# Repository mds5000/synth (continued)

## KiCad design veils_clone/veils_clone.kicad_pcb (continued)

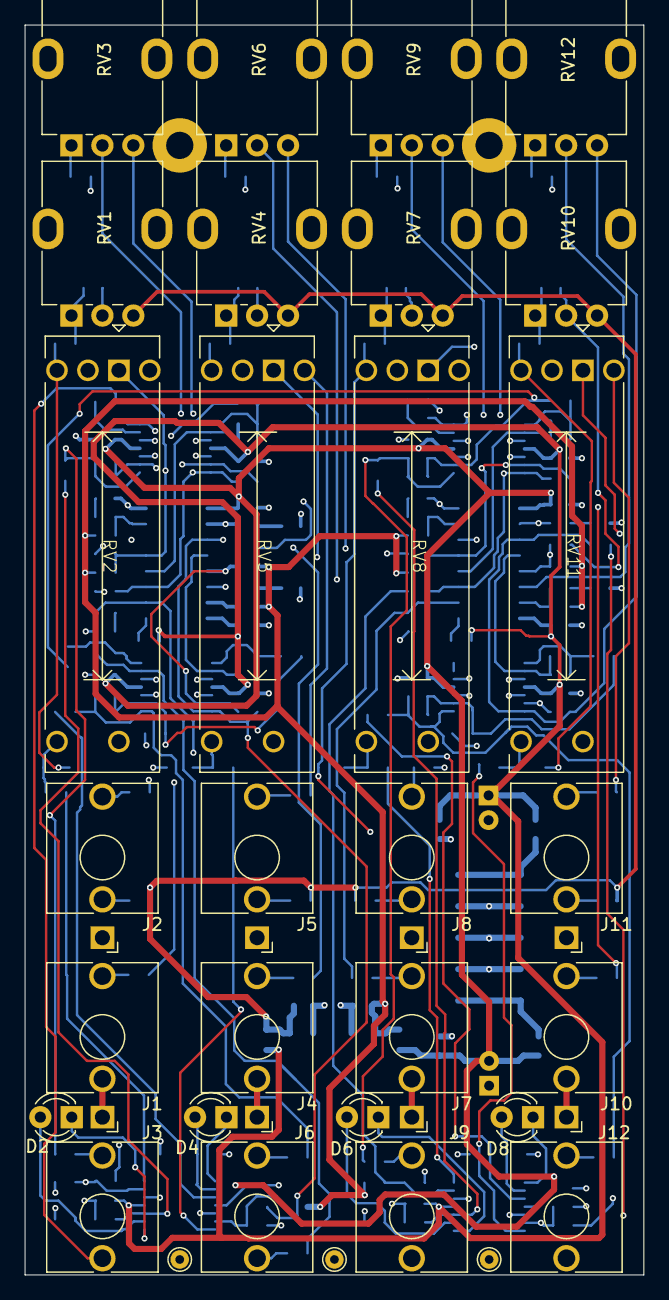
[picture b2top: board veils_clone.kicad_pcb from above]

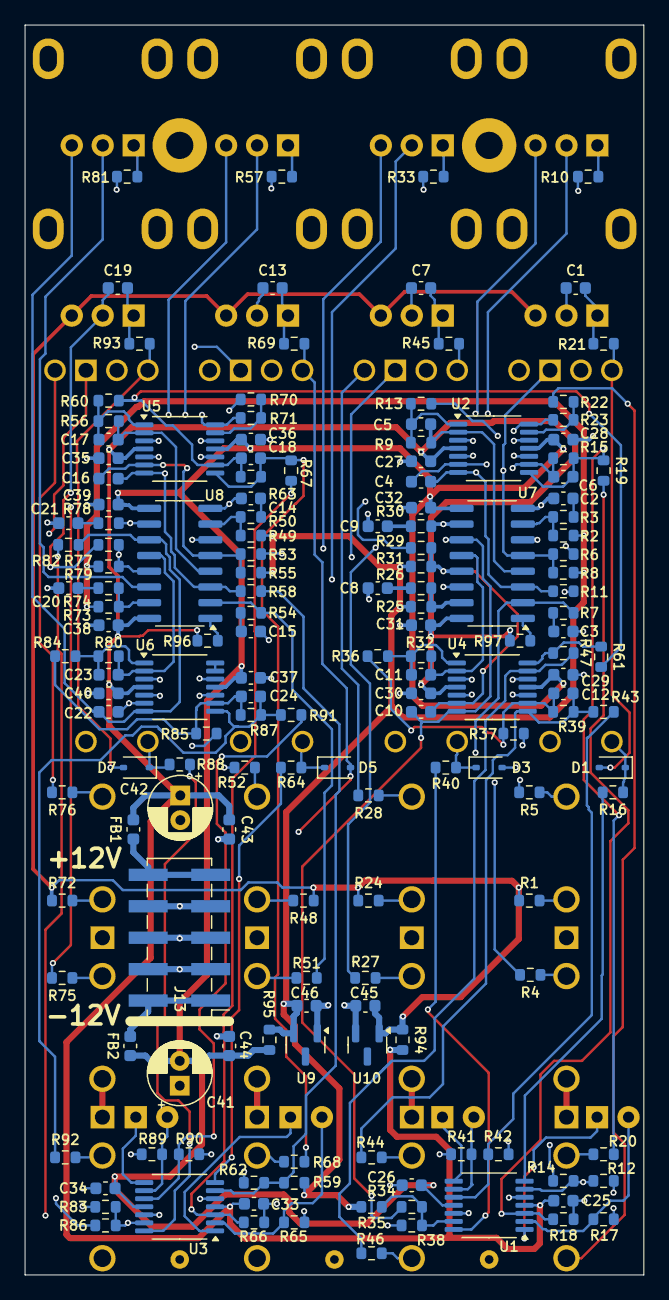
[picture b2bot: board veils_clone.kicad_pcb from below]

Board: 4 copper layers, 50.0 x 101.0 mm, 188 parts (160 on the bottom side), 119 nets.

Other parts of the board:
R71: 5.1K; R_0603_1608Metric

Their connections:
/CH3/OUT: R71.2; also elsewhere on the board
unnamed 96: R71.1; also elsewhere on the board

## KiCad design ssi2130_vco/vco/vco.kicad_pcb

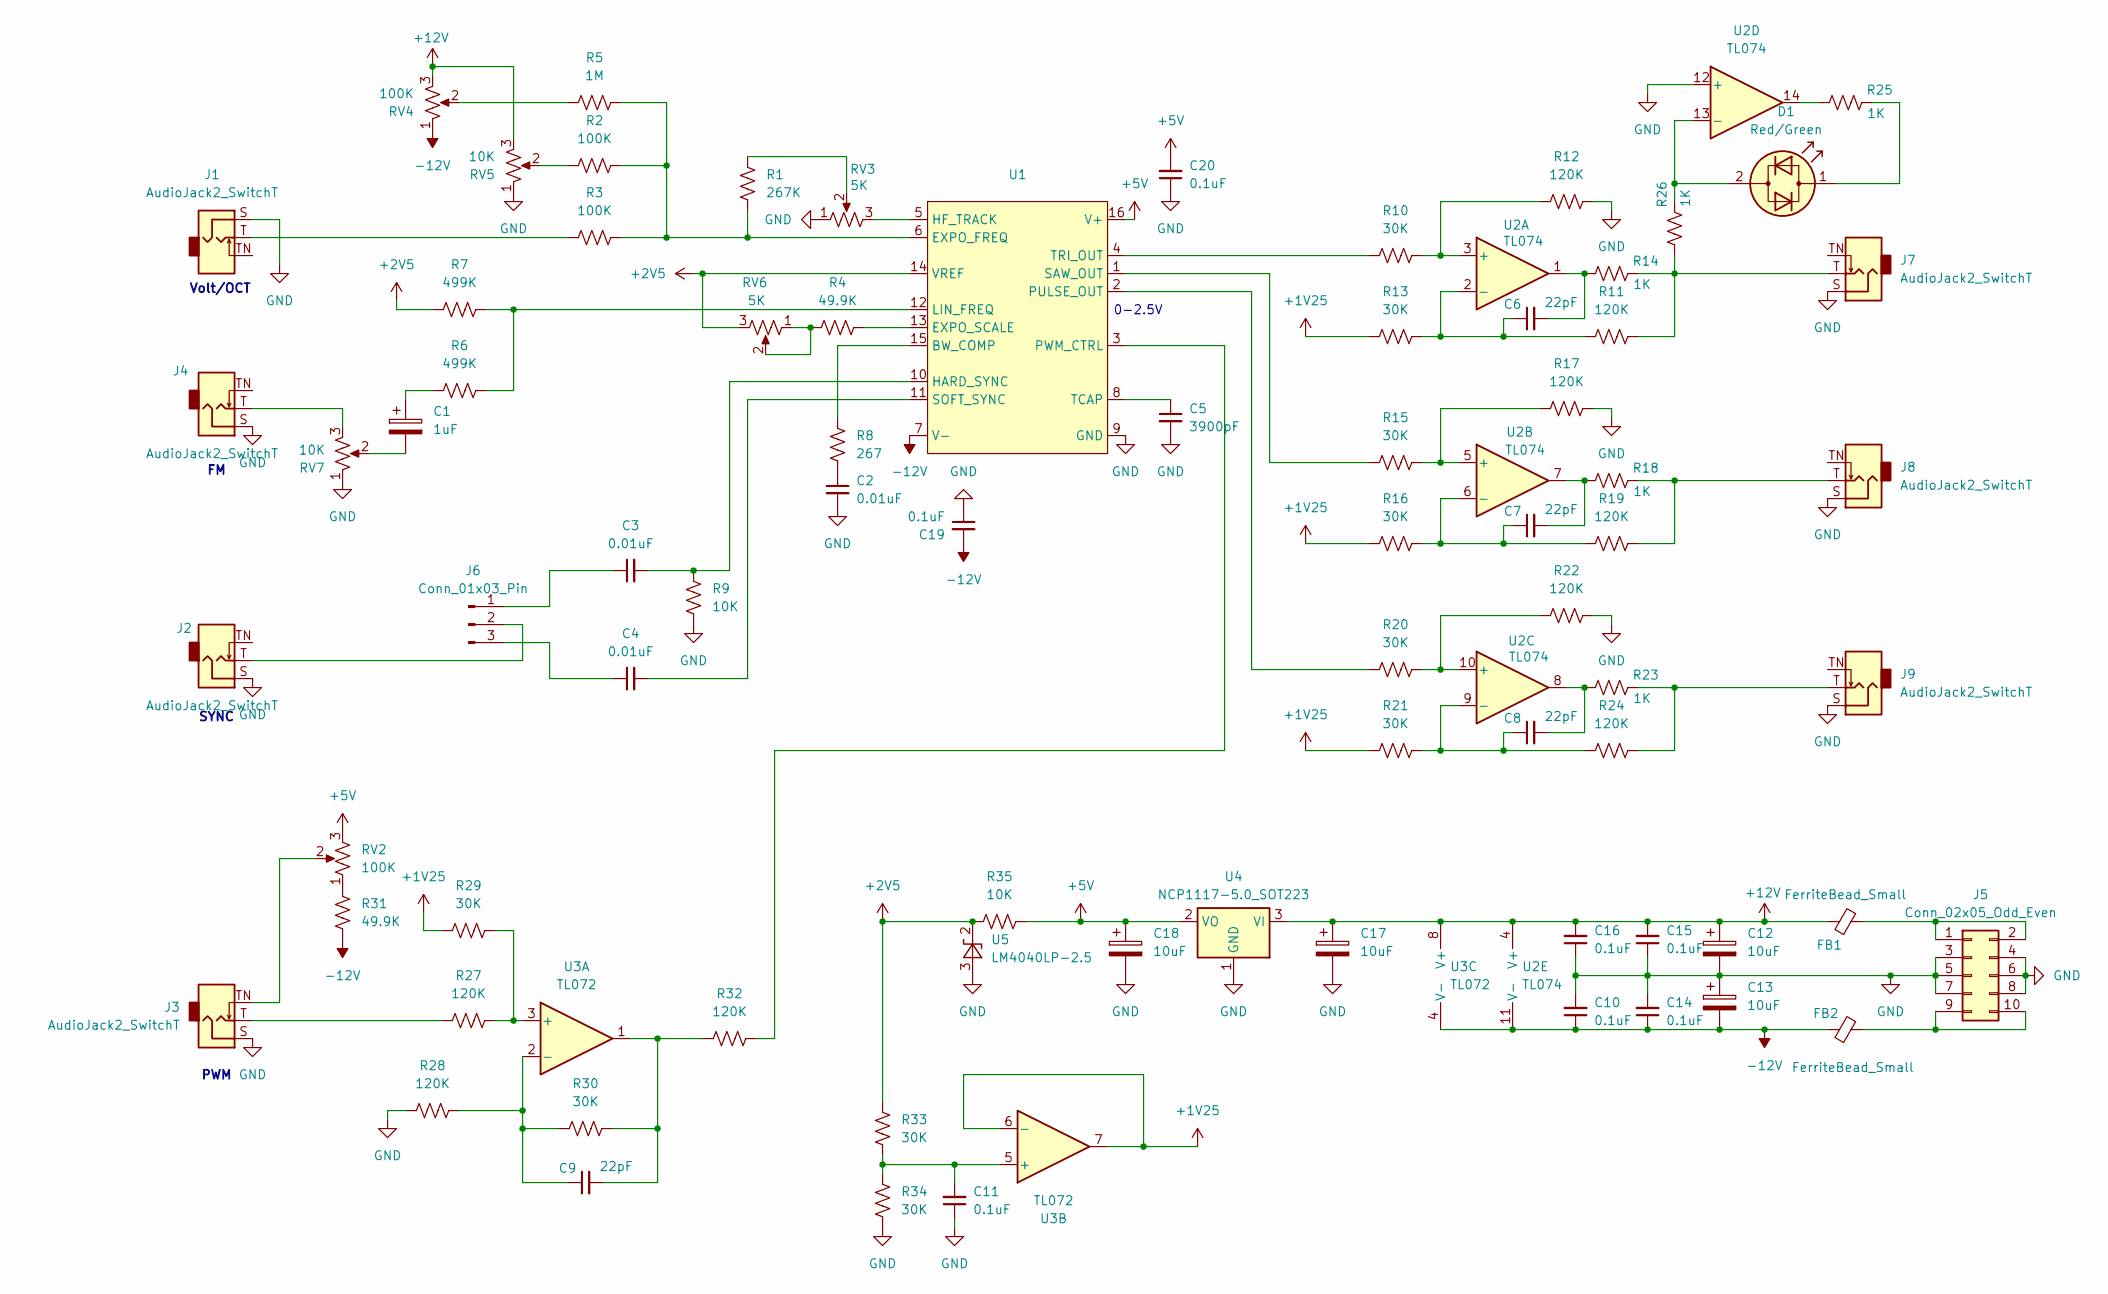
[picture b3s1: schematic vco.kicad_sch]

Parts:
C1: 1uF; CP_Radial_D5.0mm_P2.00mm
C2, C3, C4: 0.01uF; C_0603_1608Metric_Pad1.08x0.95mm_HandSolder
C5: 3900pF; C_0603_1608Metric_Pad1.08x0.95mm_HandSolder
C6, C7, C8, C9: 22pF; C_0603_1608Metric_Pad1.08x0.95mm_HandSolder
C10, C11, C14, C15, C16, C19, C20: 0.1uF; C_0603_1608Metric_Pad1.08x0.95mm_HandSolder
C12, C13, C17, C18: 10uF; CP_Radial_D5.0mm_P2.00mm
D1: Red/Green; LED_D3.0mm
FB1, FB2: FerriteBead_Small; R_0603_1608Metric_Pad0.98x0.95mm_HandSolder
J1, J2, J3, J4, J7, J8, J9: AudioJack2_SwitchT; Jack_3.5mm_QingPu_WQP-PJ398SM_Vertical_CircularHoles
J5: Conn_02x05_Odd_Even; PinHeader_2x05_P2.54mm_Vertical
J6: Conn_01x03_Pin; PinHeader_1x03_P2.54mm_Vertical
R1: 267K; R_0603_1608Metric_Pad0.98x0.95mm_HandSolder
R2, R3: 100K; R_0603_1608Metric_Pad0.98x0.95mm_HandSolder
R4, R31: 49.9K; R_0603_1608Metric_Pad0.98x0.95mm_HandSolder
R5: 1M; R_0603_1608Metric_Pad0.98x0.95mm_HandSolder
R6, R7: 499K; R_0603_1608Metric_Pad0.98x0.95mm_HandSolder
R8: 267; R_0603_1608Metric_Pad0.98x0.95mm_HandSolder
R9, R35: 10K; R_0603_1608Metric_Pad0.98x0.95mm_HandSolder
R10, R13, R15, R16, R20, R21, R29, R30, R33, R34: 30K; R_0603_1608Metric_Pad0.98x0.95mm_HandSolder
R11, R12, R17, R19, R22, R24, R27, R28, R32: 120K; R_0603_1608Metric_Pad0.98x0.95mm_HandSolder
R14, R18, R23, R25, R26: 1K; R_0603_1608Metric_Pad0.98x0.95mm_HandSolder
RV2, RV4: 100K; Potentiometer_Alpha_RD901F-40-00D_Single_Vertical
RV3, RV6: 5K; Potentiometer_Bourns_3296W_Vertical
RV5, RV7: 10K; Potentiometer_Alpha_RD901F-40-00D_Single_Vertical
U1: SOIC-16_3.9x9.9mm_P1.27mm
U2: TL074; SOIC-14_3.9x8.7mm_P1.27mm
U3: TL072; SOIC-8_3.9x4.9mm_P1.27mm
U4: NCP1117-5.0_SOT223; SOT-223-3_TabPin2
U5: LM4040LP-2.5; TO-92_Inline

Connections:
+1V25: R13.2, R16.2, R21.2, R29.2, U3.6 (-), U3.7
+2V5: R7.1, R33.1, R35.2, RV6.3, U1.14 (VREF), U5.2 (K)
+5V: C18.1, C20.2, R35.1, RV2.3, U1.16 (V+), U4.2 (VO)
+12V: C12.1, C15.2, C16.2, C17.1, FB1.1, RV4.3, RV5.3, U2.4 (V+), U3.8 (V+), U4.3 (VI)
-12V: C10.1, C13.2, C14.1, C19.2, FB2.1, R31.1, RV4.1, U1.7 (V-), U2.11 (V-), U3.4 (V-)
GND: C2.2, C5.2, C10.2, C11.1, C12.2, C13.1, C14.2, C15.1, C16.1, C17.2, C18.2, C19.1, C20.1, J1.S, J2.S, J3.S, J4.S, J5.3, J5.4, J5.5, J5.6, J5.7, J5.8, J7.S, J8.S, J9.S, R9.1, R12.1, R17.1, R22.1, R28.2, R34.2, RV3.1, RV5.1, RV7.1, U1.9 (GND), U2.12 (+), U4.1 (GND), U5.3 (A)
unnamed: C1.1, R6.1
unnamed: C1.2, RV7.2
unnamed: C2.1, R8.1
unnamed: C6.2, R14.2, U2.1
unnamed: C7.2, R18.2, U2.7
unnamed: C8.2, R23.2, U2.8
unnamed: C9.2, R30.1, R32.2, U3.1
unnamed: D1.2 (AK), R26.1, U2.13 (-)
unnamed: D1.1 (KA), R25.1
unnamed: J1.T, R3.1
unnamed: J3.T, R27.2
unnamed: J3.TN, RV2.2
unnamed: J4.T, RV7.3
unnamed: FB1.2, J5.1, J5.2
unnamed: FB2.2, J5.9, J5.10
unnamed: C3.1, J6.1
unnamed: J2.T, J6.2
unnamed: C4.1, J6.3
unnamed: J7.T, R11.1, R14.1, R26.2
unnamed: J8.T, R18.1, R19.1
unnamed: J9.T, R23.1, R24.1
unnamed: R1.2, RV3.2
unnamed: R2.1, RV5.2
unnamed: R4.1, RV6.1, RV6.2
unnamed: R5.1, RV4.2
unnamed: R25.2, U2.14
unnamed: R31.2, RV2.1
unnamed: R8.2, U1.15 (BW_COMP)
unnamed: R1.1, R2.2, R3.2, R5.2, U1.6 (EXPO_FREQ)
unnamed: R4.2, U1.13 (EXPO_SCALE)
unnamed: C3.2, R9.2, U1.10 (HARD_SYNC)
unnamed: RV3.3, U1.5 (HF_TRACK)
unnamed: R6.2, R7.2, U1.12 (LIN_FREQ)
unnamed: R20.2, U1.2 (PULSE_OUT)
unnamed: R32.1, U1.3 (PWM_CTRL)
unnamed: R15.2, U1.1 (SAW_OUT)
unnamed: C4.2, U1.11 (SOFT_SYNC)
unnamed: C5.1, U1.8 (TCAP)
unnamed: R10.2, U1.4 (TRI_OUT)
unnamed: R10.1, R12.2, U2.3 (+)
unnamed: C6.1, R11.2, R13.1, U2.2 (-)
unnamed: R15.1, R17.2, U2.5 (+)
unnamed: C7.1, R16.1, R19.2, U2.6 (-)
unnamed: R20.1, R22.2, U2.10 (+)
unnamed: C8.1, R21.1, R24.2, U2.9 (-)
unnamed: R27.1, R29.1, U3.3 (+)
unnamed: C9.1, R28.1, R30.2, U3.2 (-)
unnamed: C11.2, R33.2, R34.1, U3.5 (+)

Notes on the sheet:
0-2.5V
SYNC
Volt/OCT
PWM

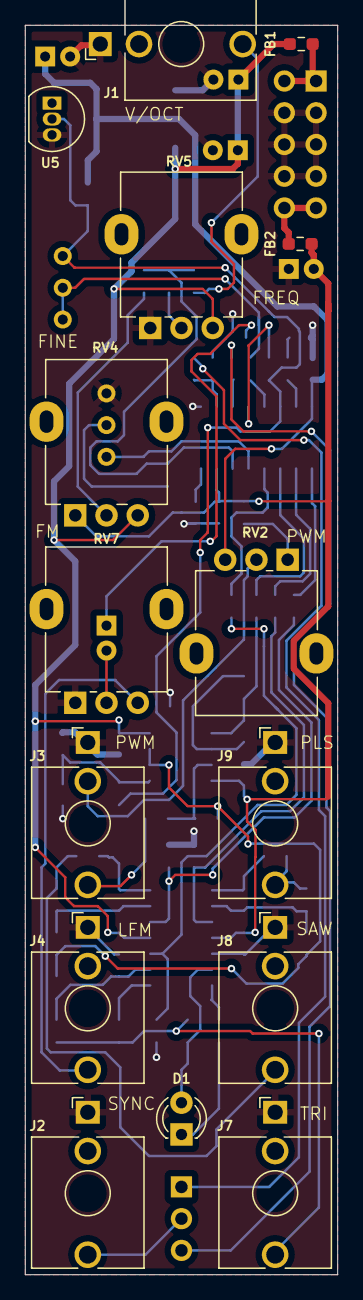
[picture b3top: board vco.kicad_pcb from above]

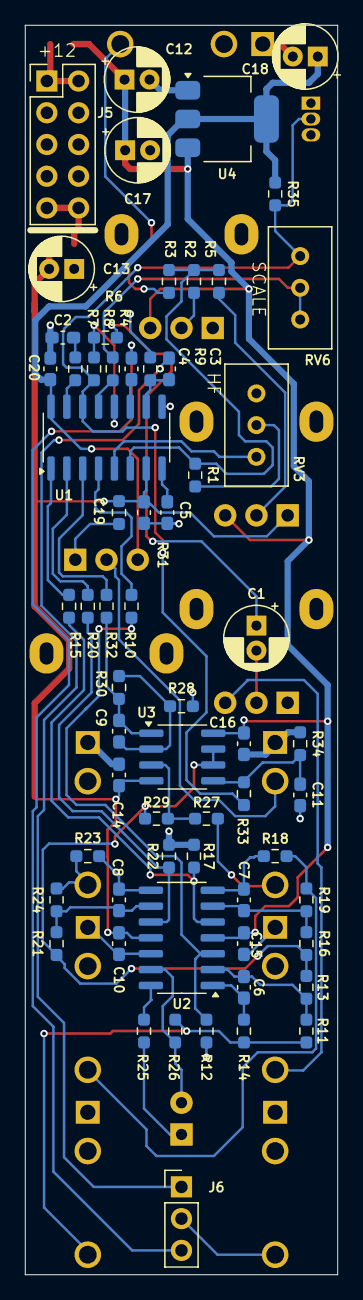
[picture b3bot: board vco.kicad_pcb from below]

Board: 2 copper layers, 25.0 x 100.0 mm, 78 parts (63 on the bottom side), 54 nets.

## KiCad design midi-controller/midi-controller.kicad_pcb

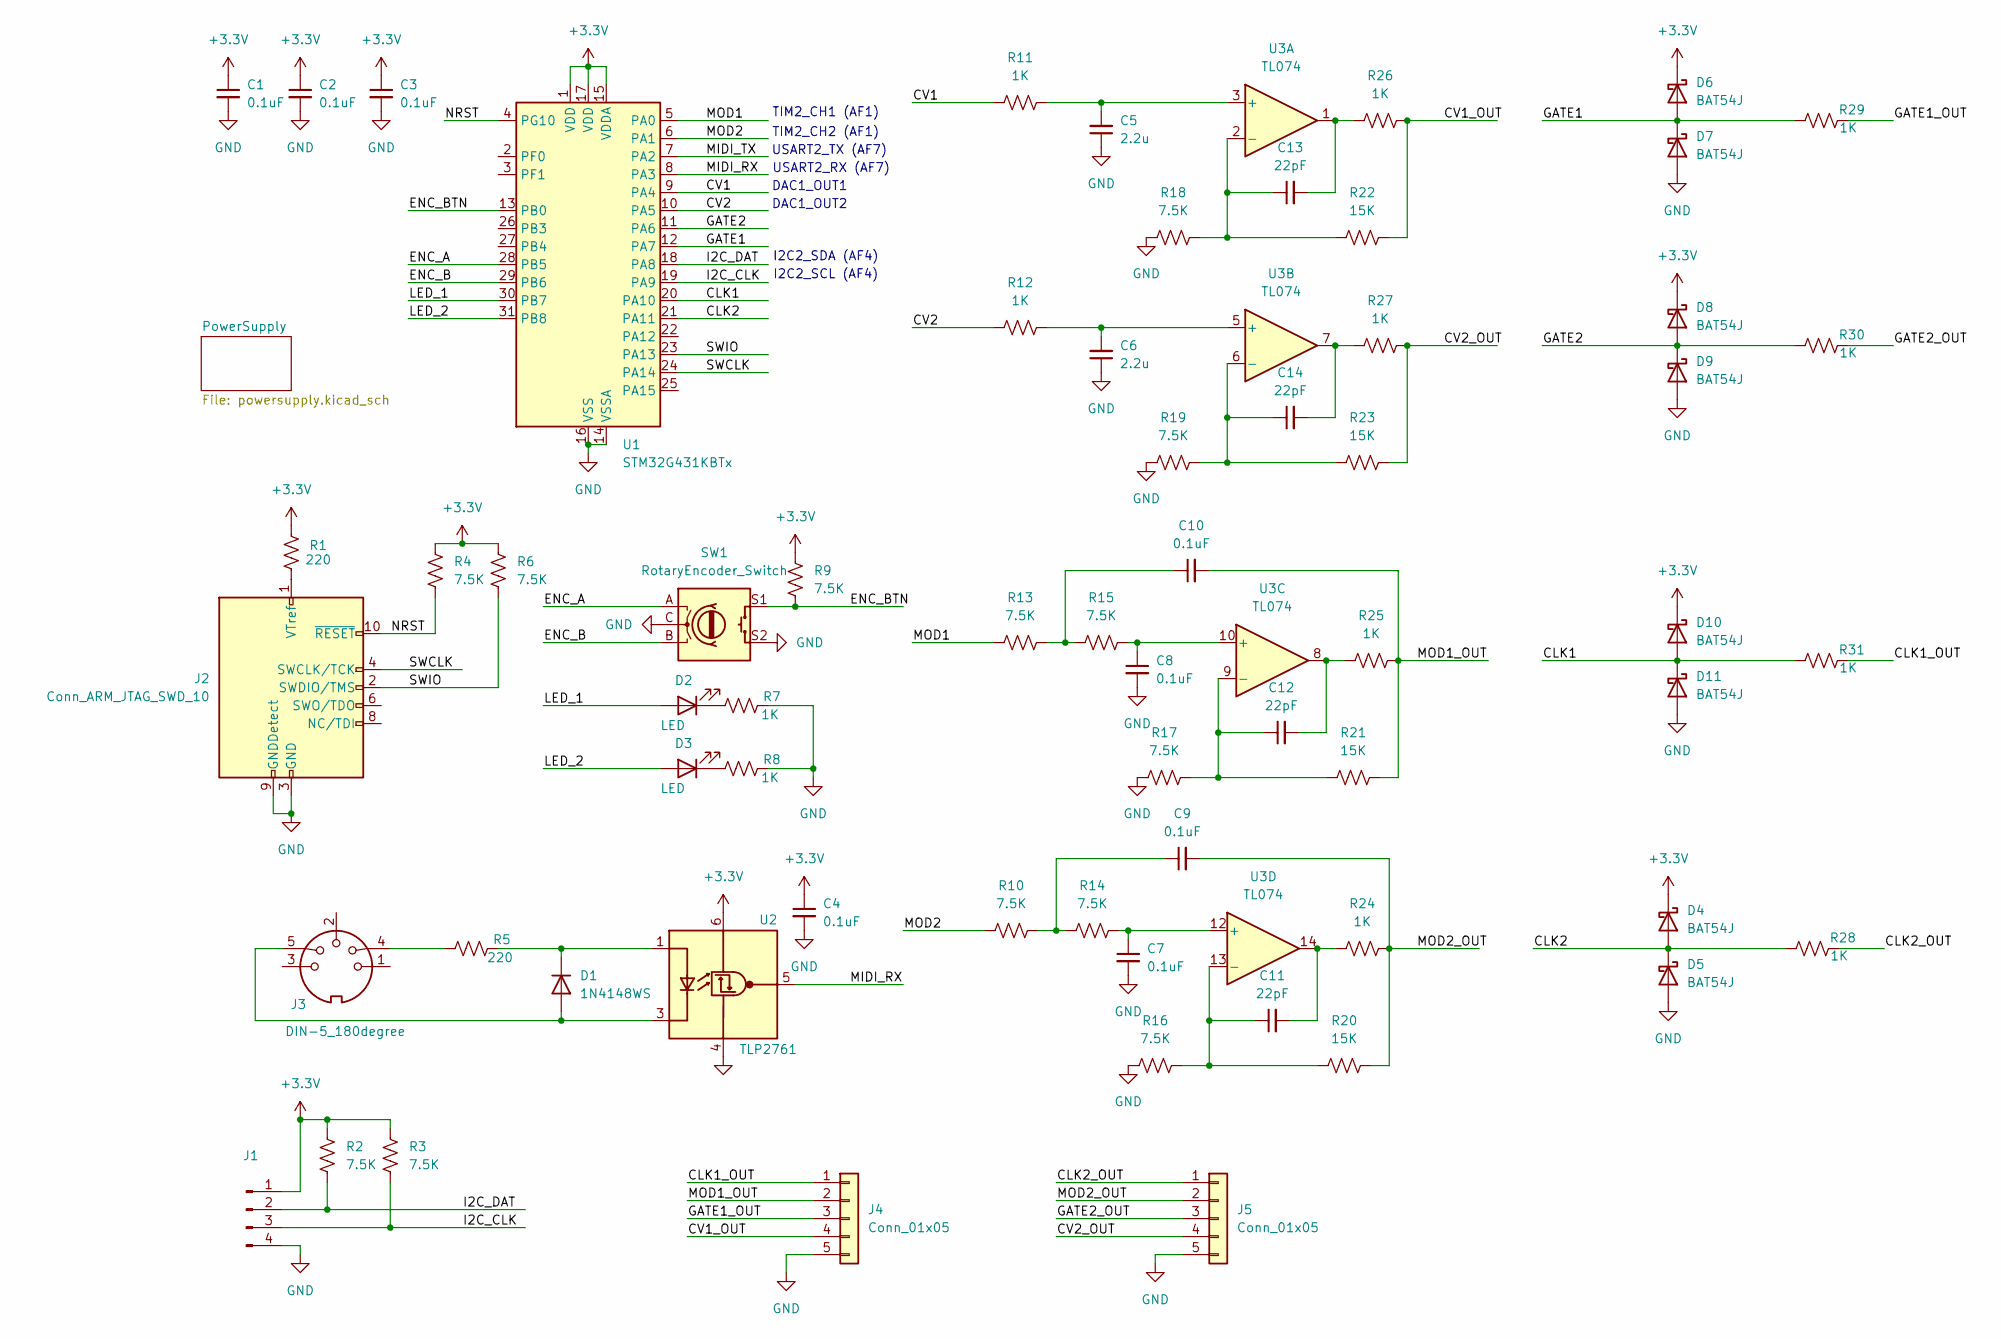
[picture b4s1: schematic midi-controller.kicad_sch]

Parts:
C1, C2, C3, C4, C7, C8, C9, C10: 0.1uF; C_0603_1608Metric
C5, C6: 2.2u; C_0805_2012Metric
C11, C12, C13, C14: 22pF; C_0603_1608Metric
D1: 1N4148WS; D_SOD-323
D2, D3: LED; LED_0603_1608Metric
D4, D5, D6, D7, D8, D9, D10, D11: BAT54J; D_SOD-323F
J1: Conn_01x04_Pin; PinHeader_1x04_P2.54mm_Vertical
J2: Conn_ARM_JTAG_SWD_10; PinHeader_2x05_P1.27mm_Vertical
J3: DIN-5_180degree; MIDI_DIN5
J4, J5: Conn_01x05; JST_XH_B5B-XH-A_1x05_P2.50mm_Vertical
R1, R5: 220; R_0603_1608Metric
R2, R3, R4, R6, R9, R10, R13, R14, R15, R16, R17, R18, R19: 7.5K; R_0603_1608Metric
R7, R8, R11, R12, R24, R25, R26, R27, R28, R29, R30, R31: 1K; R_0603_1608Metric
R20, R21, R22, R23: 15K; R_0603_1608Metric
SW1: RotaryEncoder_Switch; RotaryEncoder_Alps_EC11E-Switch_Vertical_H20mm
U1: STM32G431KBTx; LQFP-32_7x7mm_P0.8mm
U2: TLP2761; SO-6L_10x3.84mm_P1.27mm
U3: TL074; SOIC-14_3.9x8.7mm_P1.27mm

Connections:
+3.3V: C1.1, C2.1, C3.1, C4.1, D4.1 (K), D6.1 (K), D8.1 (K), D10.1 (K), J1.1, R1.1, R2.1, R3.1, R4.1, R6.1, R9.1, U1.1 (VDD), U1.15 (VDDA), U1.17 (VDD), U2.6 (VDD); also elsewhere on the board
/CLK1: D10.2 (A), D11.1 (K), R31.2, U1.20 (PA10)
/CLK1_OUT: J4.1, R31.1
/CLK2: D4.2 (A), D5.1 (K), R28.2, U1.21 (PA11)
/CLK2_OUT: J5.1, R28.1
/CV1: R11.2, U1.9 (PA4)
/CV1_OUT: J4.4, R22.1, R26.1
/CV2: R12.2, U1.10 (PA5)
/CV2_OUT: J5.4, R23.1, R27.1
/ENC_A: SW1.A, U1.28 (PB5)
/ENC_B: SW1.B, U1.29 (PB6)
/ENC_BTN: R9.2, SW1.S1, U1.13 (PB0)
/GATE1: D6.2 (A), D7.1 (K), R29.2, U1.12 (PA7)
/GATE1_OUT: J4.3, R29.1
/GATE2: D8.2 (A), D9.1 (K), R30.2, U1.11 (PA6)
/GATE2_OUT: J5.3, R30.1
/I2C_CLK: J1.3, R3.2, U1.19 (PA9)
/I2C_DAT: J1.2, R2.2, U1.18 (PA8)
/LED_1: D2.2 (A), U1.30 (PB7)
/LED_2: D3.2 (A), U1.31 (PB8)
/MIDI_RX: U1.8 (PA3), U2.5 (VO)
/MIDI_TX: U1.7 (PA2)
/MOD1: R13.2, U1.5 (PA0)
/MOD1_OUT: C10.2, J4.2, R21.1, R25.1
/MOD2: R10.2, U1.6 (PA1)
/MOD2_OUT: C9.2, J5.2, R20.1, R24.1
/NRST: J2.10 (~RESET), R4.2, U1.4 (PG10)
/SWCLK: J2.4 (SWCLK/TCK), U1.24 (PA14)
/SWIO: J2.2 (SWDIO/TMS), R6.2, U1.23 (PA13)
GND: C1.2, C2.2, C3.2, C4.2, C5.1, C6.1, C7.2, C8.2, D5.2 (A), D7.2 (A), D9.2 (A), D11.2 (A), J1.4, J2.3 (GND), J2.5 (GND), J2.9 (GNDDetect), J4.5, J5.5, R7.1, R8.1, R16.2, R17.2, R18.2, R19.2, SW1.C, SW1.S2, U1.14 (VSSA), U1.16 (VSS), U1.32 (VSS), U2.4 (GND); also elsewhere on the board
unnamed: C9.1, R10.1, R14.2
unnamed: C10.1, R13.1, R15.2
unnamed: C11.2, R24.2, U3.14
unnamed: C12.2, R25.2, U3.8
unnamed: C13.2, R26.2, U3.1
unnamed: C14.2, R27.2, U3.7
unnamed: D1.2 (A), J3.5, U2.3 (K)
unnamed: D1.1 (K), R5.1, U2.1 (A)
unnamed: D2.1 (K), R7.2
unnamed: D3.1 (K), R8.2
unnamed: J2.1 (VTref), R1.2
unnamed: J3.4, R5.2
unnamed: C5.2, R11.1, U3.3 (+)
unnamed: C13.1, R18.1, R22.2, U3.2 (-)
unnamed: C6.2, R12.1, U3.5 (+)
unnamed: C14.1, R19.1, R23.2, U3.6 (-)
unnamed: C8.1, R15.1, U3.10 (+)
unnamed: C12.1, R17.1, R21.2, U3.9 (-)
unnamed: C7.1, R14.1, U3.12 (+)
unnamed: C11.1, R16.1, R20.2, U3.13 (-)

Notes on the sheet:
DAC1_OUT1
TIM2_CH1 (AF1)
TIM2_CH2 (AF1)
USART2_TX (AF7)
USART2_RX (AF7)
DAC1_OUT2
I2C2_SDA (AF4)
I2C2_SCL (AF4)

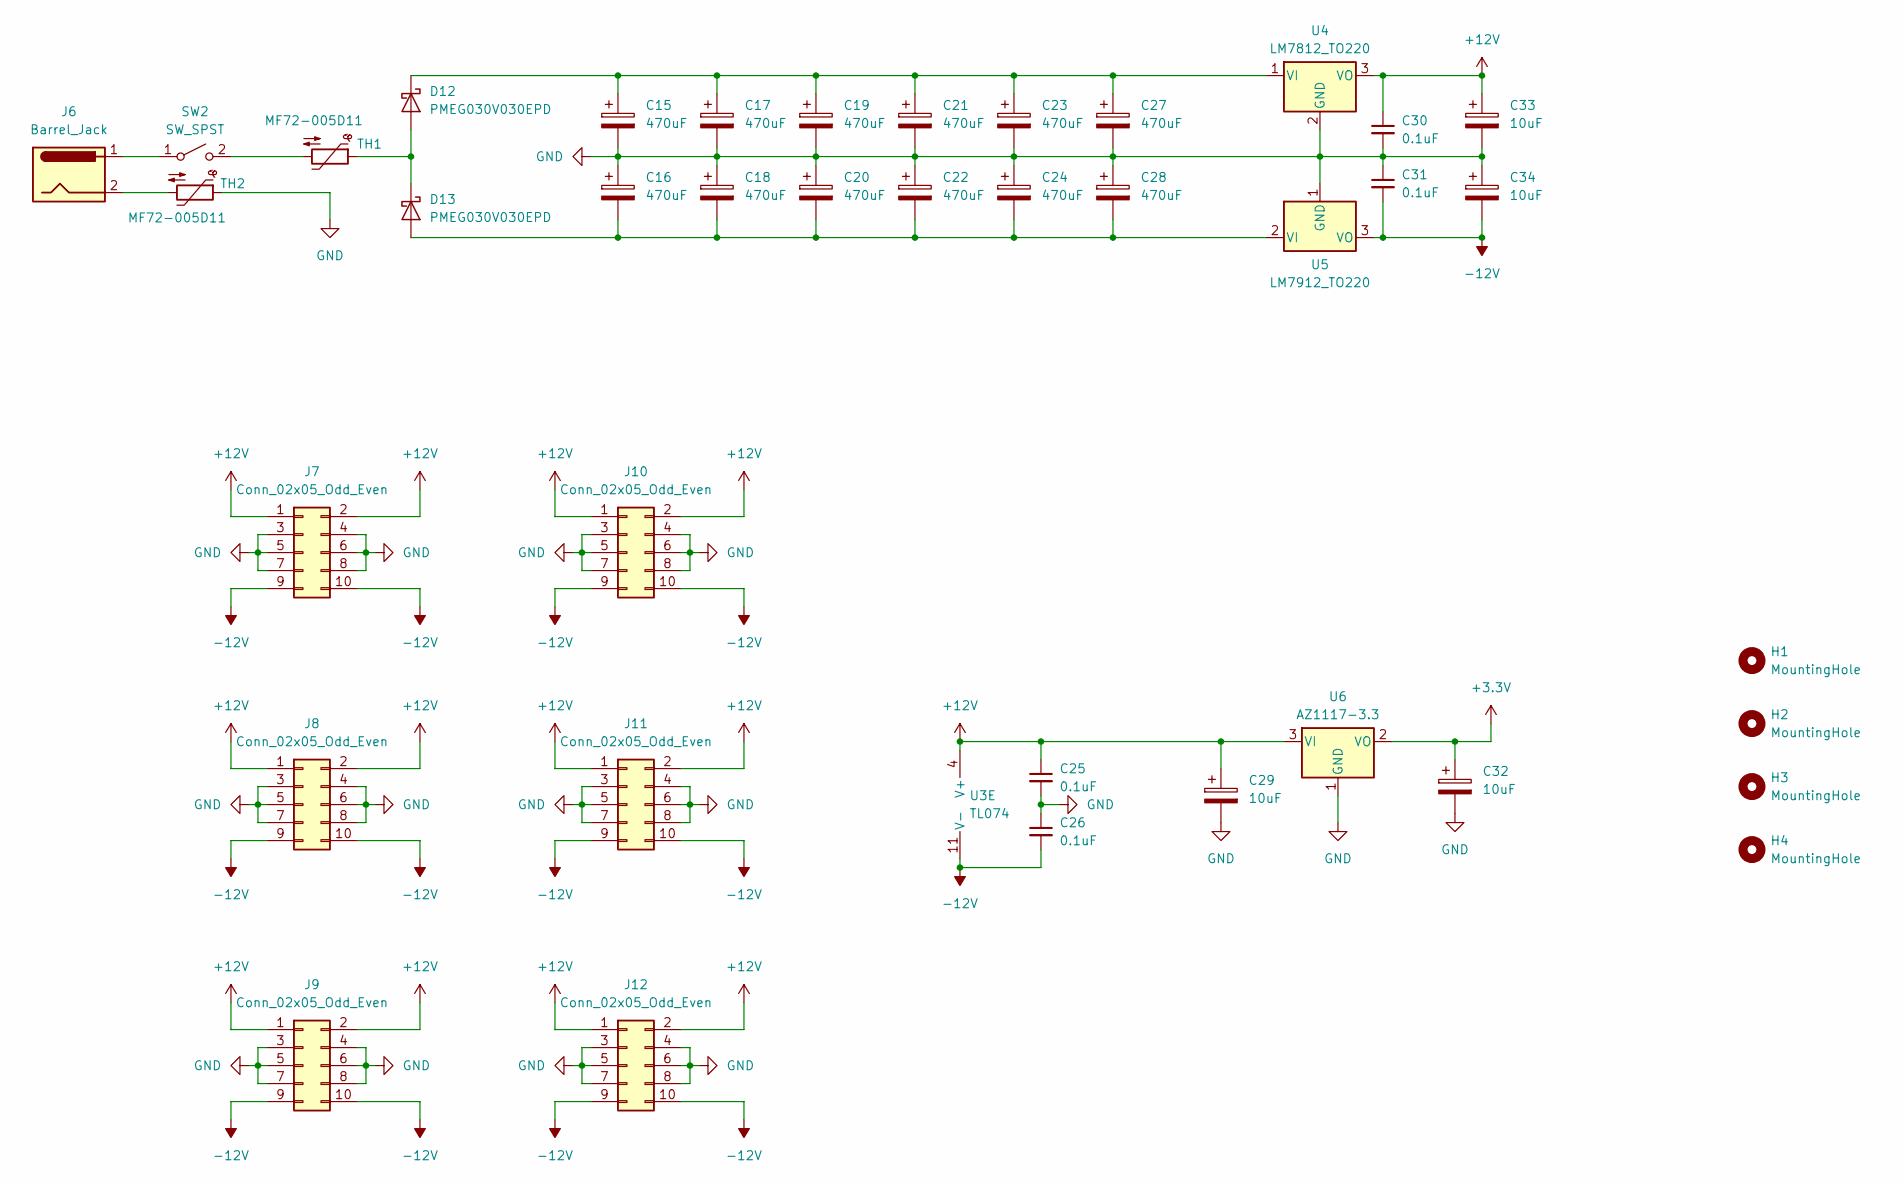
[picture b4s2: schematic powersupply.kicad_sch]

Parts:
C15, C16, C17, C18, C19, C20, C21, C22, C23, C24, C27, C28: 470uF; CP_Radial_D10.0mm_P5.00mm
C25, C26, C30, C31: 0.1uF; C_0603_1608Metric
C29, C32, C33, C34: 10uF; CP_Radial_D5.0mm_P2.00mm
D12, D13: PMEG030V030EPD; Nexperia_CFP15_SOT-1289
H1, H2, H3, H4: MountingHole; MountingHole_3.2mm_M3_Pad
J6: Barrel_Jack; BarrelJack_CUI_PJ-102AH_Horizontal
J7, J8, J9, J10, J11, J12: Conn_02x05_Odd_Even; PinHeader_2x05_P2.54mm_Vertical
SW2: SW_SPST; RA1H1C112R
TH1, TH2: MF72-005D11; RV_Disc_D12mm_W5.8mm_P7.5mm
U3: TL074; SOIC-14_3.9x8.7mm_P1.27mm
U4: LM7812_TO220; TO-220-3_Vertical
U5: LM7912_TO220; TO-220-3_Vertical
U6: AZ1117-3.3; TO-252-3_TabPin2

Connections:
+3.3V: C32.1, U6.2 (VO); also elsewhere on the board
+12V: C25.1, C29.1, C30.1, C33.1, J7.1, J7.2, J8.1, J8.2, J9.1, J9.2, J10.1, J10.2, J11.1, J11.2, J12.1, J12.2, U3.4 (V+), U4.3 (VO), U6.3 (VI)
-12V: C26.2, C31.2, C34.2, J7.9, J7.10, J8.9, J8.10, J9.9, J9.10, J10.9, J10.10, J11.9, J11.10, J12.9, J12.10, U3.11 (V-), U5.3 (VO)
GND: C15.2, C16.1, C17.2, C18.1, C19.2, C20.1, C21.2, C22.1, C23.2, C24.1, C25.2, C26.1, C27.2, C28.1, C29.2, C30.2, C31.1, C32.2, C33.2, C34.1, J7.3, J7.4, J7.5, J7.6, J7.7, J7.8, J8.3, J8.4, J8.5, J8.6, J8.7, J8.8, J9.3, J9.4, J9.5, J9.6, J9.7, J9.8, J10.3, J10.4, J10.5, J10.6, J10.7, J10.8, J11.3, J11.4, J11.5, J11.6, J11.7, J11.8, J12.3, J12.4, J12.5, J12.6, J12.7, J12.8, TH2.1, U4.2 (GND), U5.1 (GND), U6.1 (GND); also elsewhere on the board
unnamed: C15.1, C17.1, C19.1, C21.1, C23.1, C27.1, D12.3 (K), U4.1 (VI)
unnamed: D12.1 (A), D12.2 (A), D13.3 (K), TH1.1
unnamed: J6.2, TH2.2
unnamed: J6.1, SW2.1 (A)
unnamed: SW2.2 (B), TH1.2
unnamed: C16.2, C18.2, C20.2, C22.2, C24.2, C28.2, D13.1 (A), D13.2 (A), U5.2 (VI)

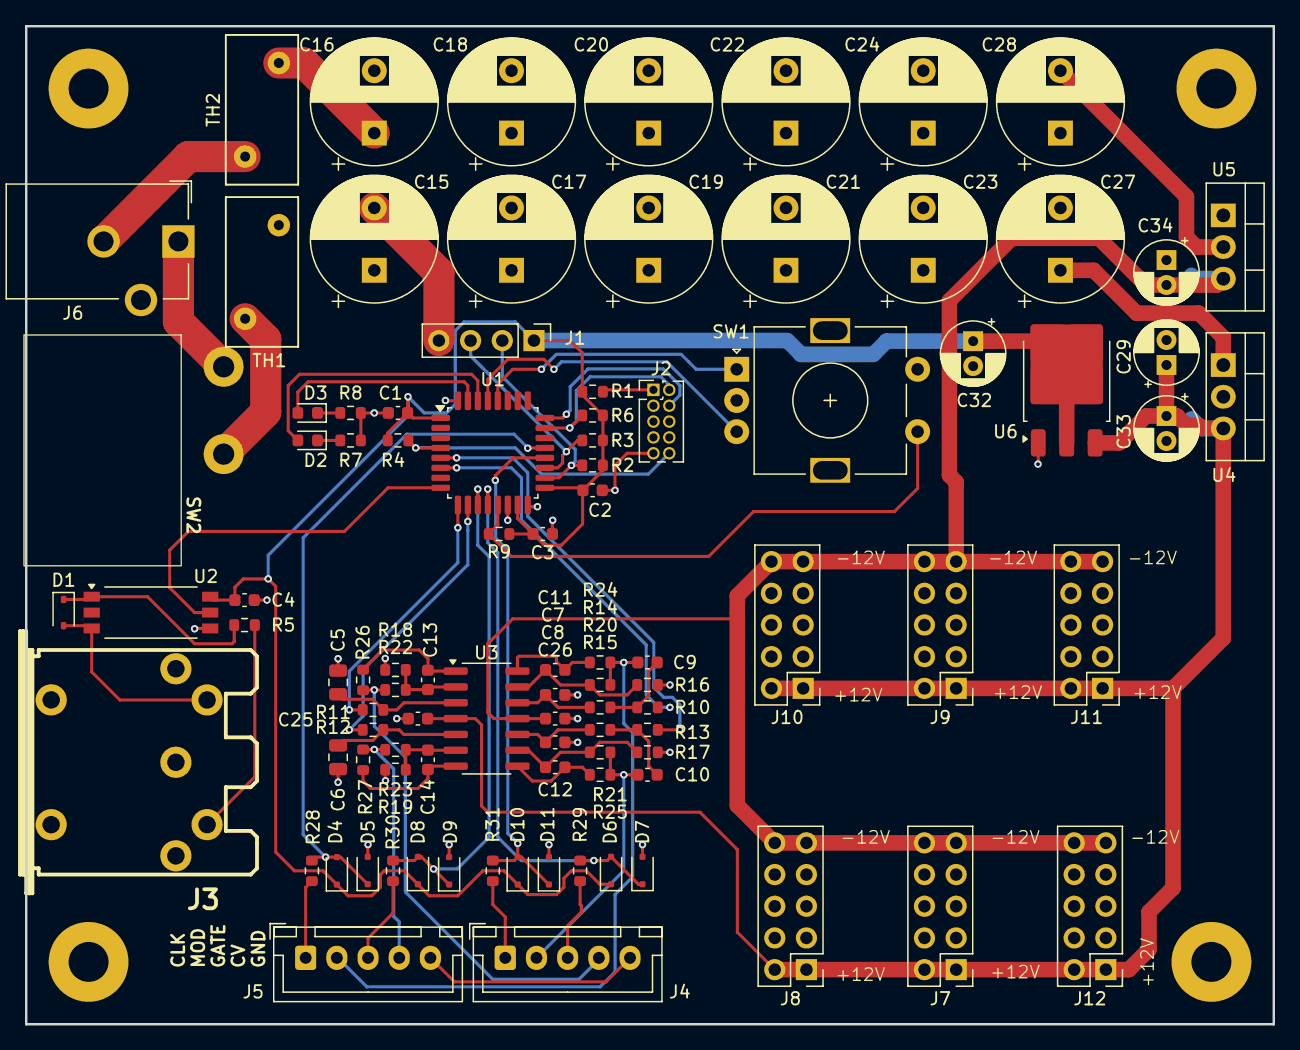
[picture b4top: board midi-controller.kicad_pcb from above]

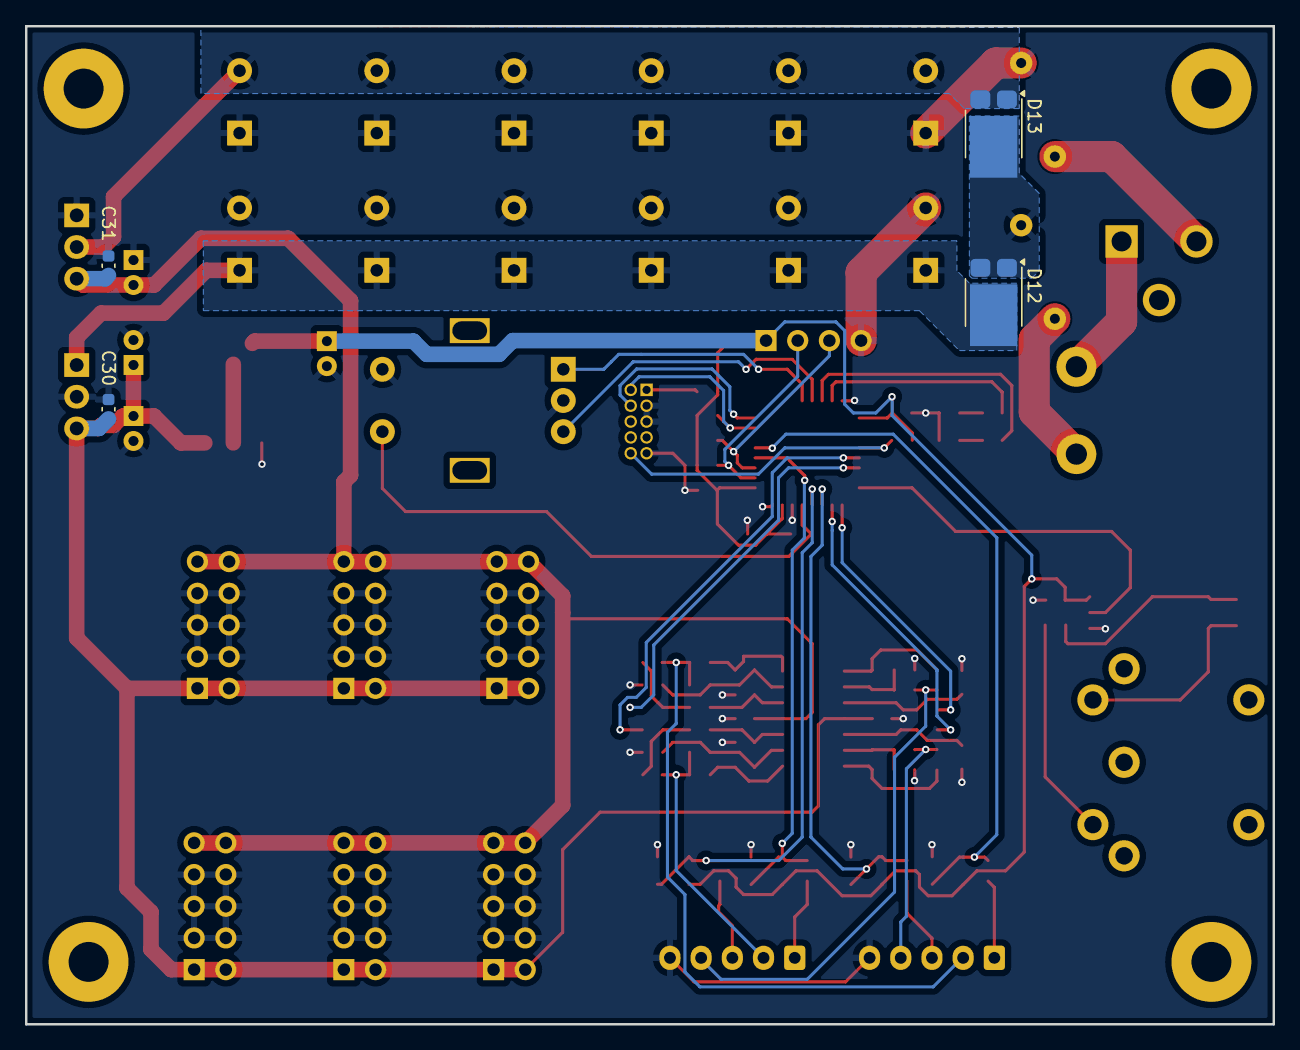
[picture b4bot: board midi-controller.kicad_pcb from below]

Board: 2 copper layers, 100.0 x 80.0 mm, 104 parts (4 on the bottom side), 57 nets.

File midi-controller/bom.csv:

"Reference","Value","Datasheet","Footprint","Qty","DNP"
"C1,C2,C3,C4,C7,C8,C9,C10,C25,C26,C30,C31","0.1uF","~","Capacitor_SMD:C_0603_1608Metric","12",""
"C5,C6","2.2u","~","Capacitor_SMD:C_0805_2012Metric","2",""
"C11,C12,C13,C14","22pF","~","Capacitor_SMD:C_0603_1608Metric","4",""
"C15,C16,C17,C18,C19,C20,C21,C22,C23,C24,C27,C28","470uF","~","Capacitor_THT:CP_Radial_D10.0mm_P5.00mm","12",""
"C29,C32,C33,C34","10uF","~","Capacitor_THT:CP_Radial_D5.0mm_P2.00mm","4",""
"D1","1N4148WS","https://www.vishay.com/docs/85751/1n4148ws.pdf","Diode_SMD:D_SOD-323","1",""
"D2,D3","LED","~","LED_SMD:LED_0603_1608Metric","2",""
"D4,D5,D6,D7,D8,D9,D10,D11","BAT54J","https://assets.nexperia.com/documents/data-sheet/BAT54J.pdf","Diode_SMD:D_SOD-323F","8",""
"D12,D13","PMEG030V030EPD","https://assets.nexperia.com/documents/data-sheet/PMEG030V030EPD.pdf","Package_TO_SOT_SMD:Nexperia_CFP15_SOT-1289","2",""
"H1,H2,H3,H4","MountingHole","~","MountingHole:MountingHole_3.2mm_M3_Pad","4",""
"J1","Conn_01x04_Pin","~","Connector_PinHeader_2.54mm:PinHeader_1x04_P2.54mm_Vertical","1",""
"J2","Conn_ARM_JTAG_SWD_10","http://infocenter.arm.com/help/topic/com.arm.doc.ddi0314h/DD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","Connector_PinHeader_1.27mm:PinHeader_2x05_P1.27mm_Vertical","1",""
"J3","DIN-5_180degree","http://www.mouser.com/ds/2/18/40_c091_abd_e-75918.pdf","Eurocad:MIDI_DIN5","1",""
"J4,J5","Conn_01x05","~","Connector_JST:JST_XH_B5B-XH-A_1x05_P2.50mm_Vertical","2",""
"J6","Barrel_Jack","~","Connector_BarrelJack:BarrelJack_CUI_PJ-102AH_Horizontal","1",""
"J7,J8,J9,J10,J11,J12","Conn_02x05_Odd_Even","~","Connector_PinHeader_2.54mm:PinHeader_2x05_P2.54mm_Vertical","6",""
"R1,R5","220","~","Resistor_SMD:R_0603_1608Metric","2",""
"R2,R3,R4,R6,R9,R10,R13,R14,R15,R16,R17,R18,R19","7.5K","~","Resistor_SMD:R_0603_1608Metric","13",""
"R7,R8,R11,R12,R24,R25,R26,R27,R28,R29,R30,R31","1K","~","Resistor_SMD:R_0603_1608Metric","12",""
"R20,R21,R22,R23","15K","~","Resistor_SMD:R_0603_1608Metric","4",""
"SW1","RotaryEncoder_Switch","~","Rotary_Encoder:RotaryEncoder_Alps_EC11E-Switch_Vertical_H20mm","1",""
"SW2","SW_SPST","~","Eurocad:RA1H1C112R","1",""
"TH1,TH2","MF72-005D11","~","Varistor:RV_Disc_D12mm_W5.8mm_P7.5mm","2",""
"U1","STM32G431KBTx","https://www.st.com/resource/en/datasheet/stm32g431kb.pdf","Package_QFP:LQFP-32_7x7mm_P0.8mm","1",""
"U2","TLP2761","https://toshiba.semicon-storage.com/info/docget.jsp?did=2881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","Package_SO:SO-6L_10x3.84mm_P1.27mm","1",""
"U3","TL074","http://www.ti.com/lit/ds/symlink/tl071.pdf","Package_SO:SOIC-14_3.9x8.7mm_P1.27mm","1",""
"U4","LM7812_TO220","https://www.onsemi.cn/PowerSolutions/document/MC7800-D.PDF","Package_TO_SOT_THT:TO-220-3_Vertical","1",""
"U5","LM7912_TO220","hhttps://www.onsemi.com/pub/Collateral/MC7900-D.PDF","Package_TO_SOT_THT:TO-220-3_Vertical","1",""
"U6","AZ1117-3.3","https://www.diodes.com/assets/Datasheets/AZ1117.pdf","Package_TO_SOT_SMD:TO-252-3_TabPin2","1",""
